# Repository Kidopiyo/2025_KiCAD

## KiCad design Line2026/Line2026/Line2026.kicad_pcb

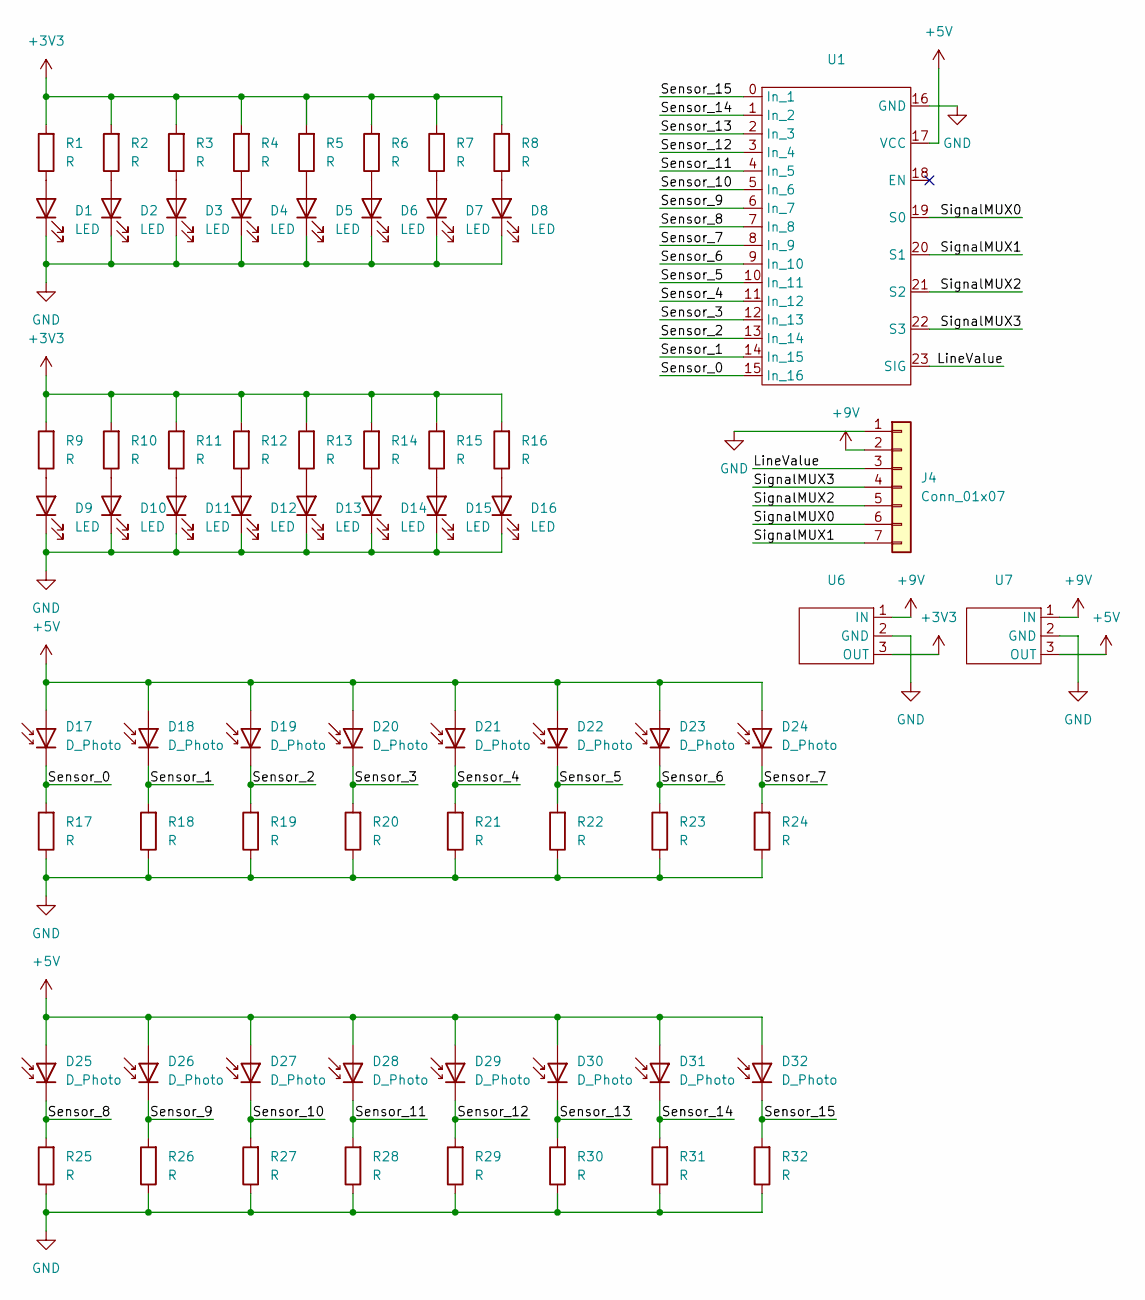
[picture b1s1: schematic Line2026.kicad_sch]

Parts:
D1, D2, D3, D4, D5, D6, D7, D8, D9, D10, D11, D12, D13, D14, D15, D16: LED; LED_D3.0mm
D17, D18, D19, D20, D21, D22, D23, D24, D25, D26, D27, D28, D29, D30, D31, D32: D_Photo; LED_D3.0mm
J4: Conn_01x07; JST_XA_B07B-XASK-1-A_1x07_P2.50mm_Vertical
R1, R2, R3, R4, R5, R6, R7, R8, R9, R10, R11, R12, R13, R14, R15, R16, R17, R18, R19, R20, R21, R22, R23, R24, R25, R26, R27, R28, R29, R30, R31, R32: R; R_Axial_DIN0207_L6.3mm_D2.5mm_P7.62mm_Horizontal
U1: BOB-09056
U6, U7: Akiduki_Converter

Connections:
+3V3: R1.2, R2.2, R3.2, R4.2, R5.2, R6.2, R7.2, R8.2, R9.2, R10.2, R11.2, R12.2, R13.2, R14.2, R15.2, R16.2, U6.3 (OUT)
+5V: D17.2 (A), D18.2 (A), D19.2 (A), D20.2 (A), D21.2 (A), D22.2 (A), D23.2 (A), D24.2 (A), D25.2 (A), D26.2 (A), D27.2 (A), D28.2 (A), D29.2 (A), D30.2 (A), D31.2 (A), D32.2 (A), U1.17 (VCC), U7.3 (OUT)
+9V: J4.2, U6.1 (IN), U7.1 (IN)
/LineValue: J4.3, U1.23 (SIG)
/Sensor_0: D17.1 (K), R17.2, U1.15 (In_16)
/Sensor_1: D18.1 (K), R18.2, U1.14 (In_15)
/Sensor_2: D19.1 (K), R19.2, U1.13 (In_14)
/Sensor_3: D20.1 (K), R20.2, U1.12 (In_13)
/Sensor_4: D21.1 (K), R21.2, U1.11 (In_12)
/Sensor_5: D22.1 (K), R22.2, U1.10 (In_11)
/Sensor_6: D23.1 (K), R23.2, U1.9 (In_10)
/Sensor_7: D24.1 (K), R24.2, U1.8 (In_9)
/Sensor_8: D25.1 (K), R25.2, U1.7 (In_8)
/Sensor_9: D26.1 (K), R26.2, U1.6 (In_7)
/Sensor_10: D27.1 (K), R27.2, U1.5 (In_6)
/Sensor_11: D28.1 (K), R28.2, U1.4 (In_5)
/Sensor_12: D29.1 (K), R29.2, U1.3 (In_4)
/Sensor_13: D30.1 (K), R30.2, U1.2 (In_3)
/Sensor_14: D31.1 (K), R31.2, U1.1 (In_2)
/Sensor_15: D32.1 (K), R32.2, U1.0 (In_1)
/SignalMUX0: J4.6, U1.19 (S0)
/SignalMUX1: J4.7, U1.20 (S1)
/SignalMUX2: J4.5, U1.21 (S2)
/SignalMUX3: J4.4, U1.22 (S3)
GND: D1.1 (K), D2.1 (K), D3.1 (K), D4.1 (K), D5.1 (K), D6.1 (K), D7.1 (K), D8.1 (K), D9.1 (K), D10.1 (K), D11.1 (K), D12.1 (K), D13.1 (K), D14.1 (K), D15.1 (K), D16.1 (K), J4.1, R17.1, R18.1, R19.1, R20.1, R21.1, R22.1, R23.1, R24.1, R25.1, R26.1, R27.1, R28.1, R29.1, R30.1, R31.1, R32.1, U1.16 (GND), U6.2 (GND), U7.2 (GND)
unnamed: D1.2 (A), R1.1
unnamed: D2.2 (A), R2.1
unnamed: D3.2 (A), R3.1
unnamed: D4.2 (A), R4.1
unnamed: D5.2 (A), R5.1
unnamed: D6.2 (A), R6.1
unnamed: D7.2 (A), R7.1
unnamed: D8.2 (A), R8.1
unnamed: D9.2 (A), R9.1
unnamed: D10.2 (A), R10.1
unnamed: D11.2 (A), R11.1
unnamed: D12.2 (A), R12.1
unnamed: D13.2 (A), R13.1
unnamed: D14.2 (A), R14.1
unnamed: D15.2 (A), R15.1
unnamed: D16.2 (A), R16.1

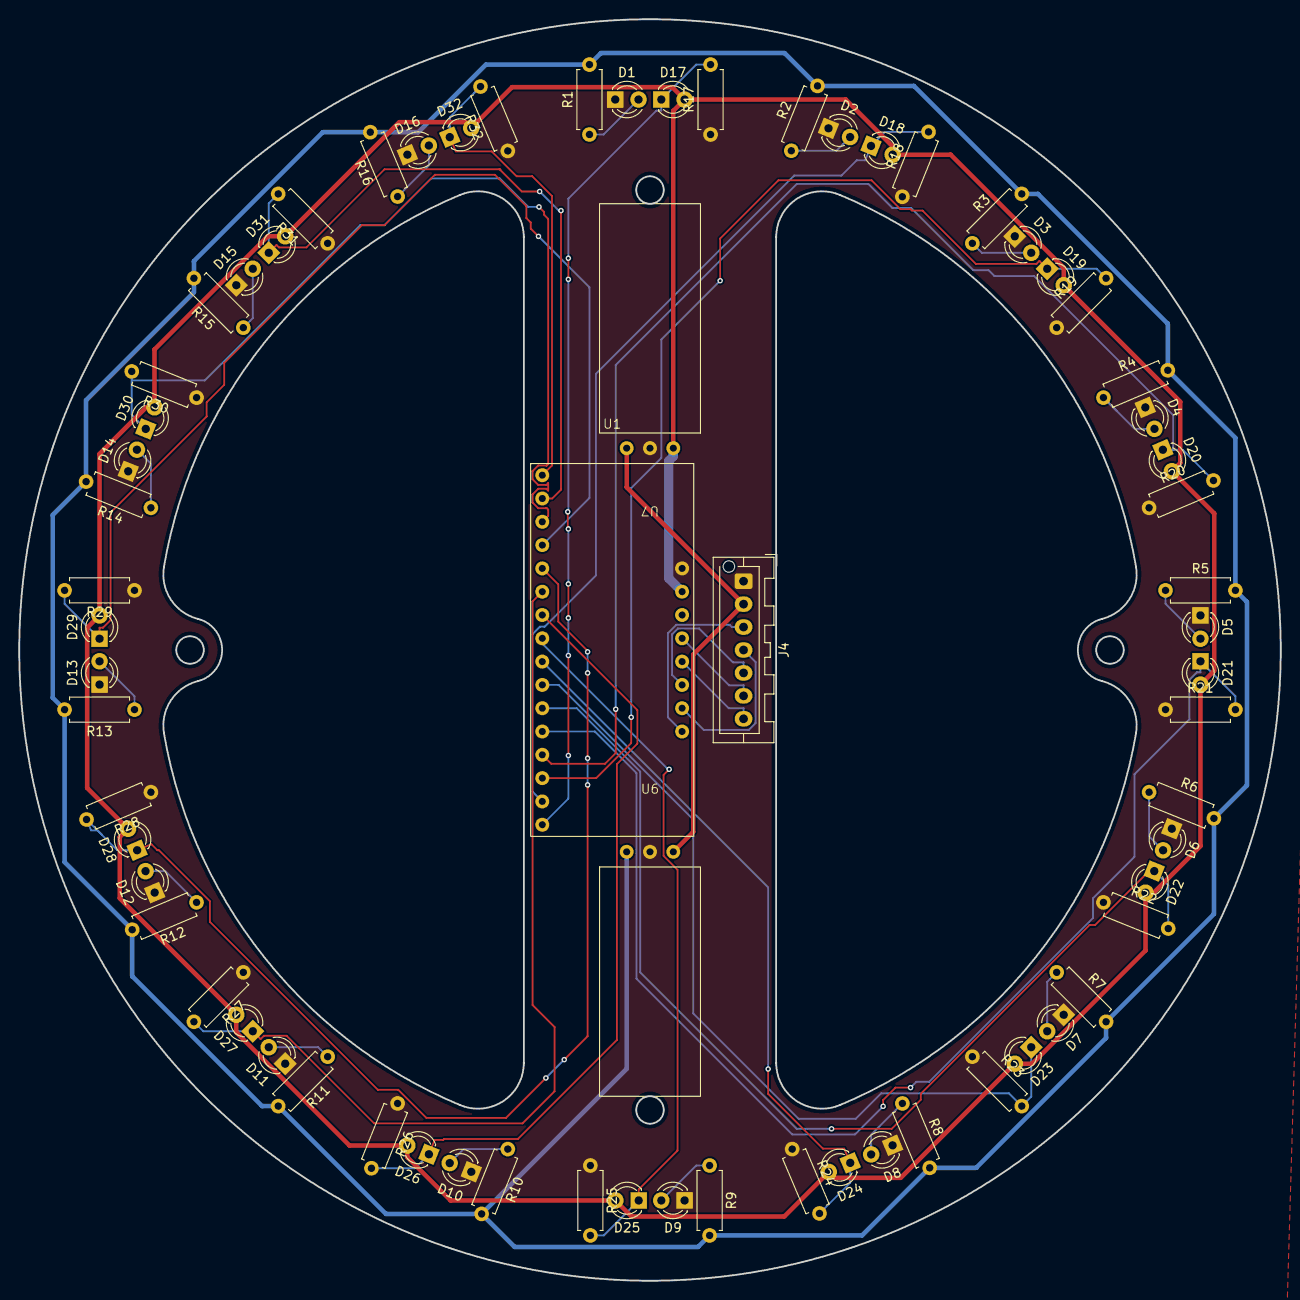
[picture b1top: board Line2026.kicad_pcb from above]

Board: 2 copper layers, 137.5 x 137.5 mm, 68 parts (0 on the bottom side), 41 nets.

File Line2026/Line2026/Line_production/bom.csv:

Designator,Footprint,Quantity,Value,LCSC Part #
"D1, D10, D11, D12, D13, D14, D15, D16, D2, D3, D4, D5, D6, D7, D8, D9",LED_D3.0mm,16,LED,
"D17, D18, D19, D20, D21, D22, D23, D24, D25, D26, D27, D28, D29, D30, D31, D32",LED_D3.0mm,16,D_Photo,
J4,JST_XA_B07B-XASK-1-A_1x07_P2.50mm_Vertical,1,Conn_01x07,
"R1, R10, R11, R12, R13, R14, R15, R16, R17, R18, R19, R2, R20, R21, R22, R23, R24, R25, R26, R27, R28, R29, R3, R30, R31, R32, R4, R5, R6, R7, R8, R9",R_Axial_DIN0207_L6.3mm_D2.5mm_P7.62mm_Horizontal,32,R,
U1,BOB-09056,1,~,
"U6, U7",Akiduki_Converter,2,~,

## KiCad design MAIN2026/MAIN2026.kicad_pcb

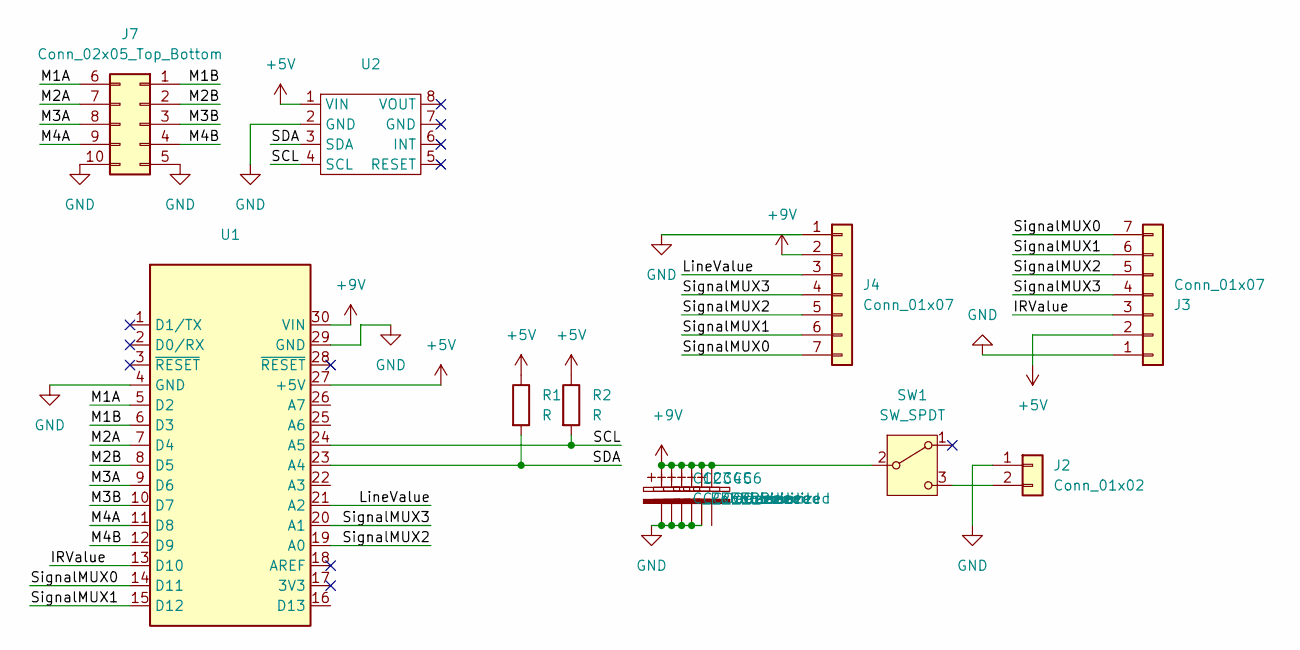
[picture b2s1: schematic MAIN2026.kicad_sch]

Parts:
C1, C2, C3, C4, C5, C6: C_Polarized; CP_Radial_D8.0mm_P2.50mm
J2: Conn_01x02; JST_XA_B02B-XASK-1-A_1x02_P2.50mm_Vertical
J3, J4: Conn_01x07; JST_XA_B07B-XASK-1-A_1x07_P2.50mm_Vertical
J7: Conn_02x05_Top_Bottom; XAD_5x2
R1, R2: R; R_Axial_DIN0207_L6.3mm_D2.5mm_P7.62mm_Horizontal
SW1: SW_SPDT; PinHeader_1x03_P2.54mm_Vertical
U1: Arduino_Nano
U2: BNO055

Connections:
+5V: J3.2, R1.1, R2.1, U1.27 (+5V), U2.1 (VIN)
+9V: C1.1, C2.1, C3.1, C4.1, C5.1, C6.1, J4.2, SW1.2 (B), U1.30 (VIN)
/IRValue: J3.3, U1.13 (D10)
/LineValue: J4.3, U1.21 (A2)
/M1A: J7.6, U1.5 (D2)
/M1B: J7.1, U1.6 (D3)
/M2A: J7.7, U1.7 (D4)
/M2B: J7.2, U1.8 (D5)
/M3A: J7.8, U1.9 (D6)
/M3B: J7.3, U1.10 (D7)
/M4A: J7.9, U1.11 (D8)
/M4B: J7.4, U1.12 (D9)
/SCL: R2.2, U1.24 (A5), U2.4 (SCL)
/SDA: R1.2, U1.23 (A4), U2.3 (SDA)
/SignalMUX0: J3.7, J4.7, U1.14 (D11)
/SignalMUX1: J3.6, J4.6, U1.15 (D12)
/SignalMUX2: J3.5, J4.5, U1.19 (A0)
/SignalMUX3: J3.4, J4.4, U1.20 (A1)
GND: C1.2, C2.2, C3.2, C4.2, C5.2, J2.1, J3.1, J4.1, J7.5, J7.10, U1.4 (GND), U1.29 (GND), U2.2 (GND)
unnamed: J2.2, SW1.3 (C)

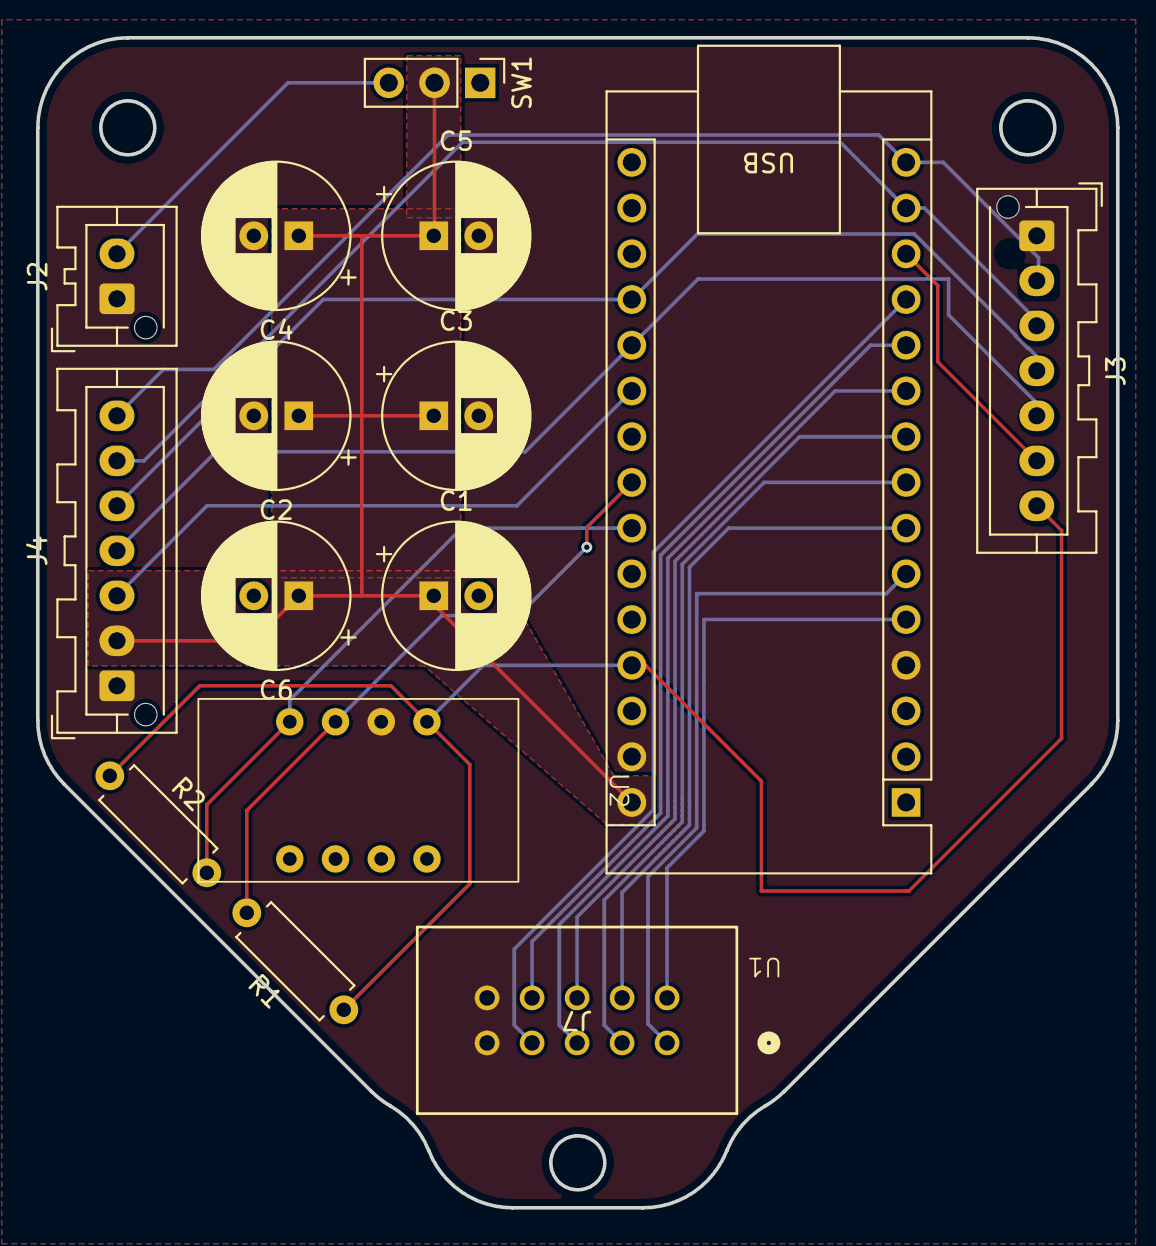
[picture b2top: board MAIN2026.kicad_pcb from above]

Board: 2 copper layers, 60.0 x 65.0 mm, 15 parts (0 on the bottom side), 20 nets.

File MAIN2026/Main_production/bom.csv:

Designator,Footprint,Quantity,Value,LCSC Part #
"C1, C2, C3, C4, C5, C6",CP_Radial_D8.0mm_P2.50mm,6,C_Polarized,
J2,JST_XA_B02B-XASK-1-A_1x02_P2.50mm_Vertical,1,Conn_01x02,
"J3, J4",JST_XA_B07B-XASK-1-A_1x07_P2.50mm_Vertical,2,Conn_01x07,
J7,XAD_5x2,1,Conn_02x05_Top_Bottom,
"R1, R2",R_Axial_DIN0207_L6.3mm_D2.5mm_P7.62mm_Horizontal,2,R,
SW1,PinHeader_1x03_P2.54mm_Vertical,1,SW_SPDT,
U1,Arduino_Nano,1,~,
U2,BNO055,1,~,

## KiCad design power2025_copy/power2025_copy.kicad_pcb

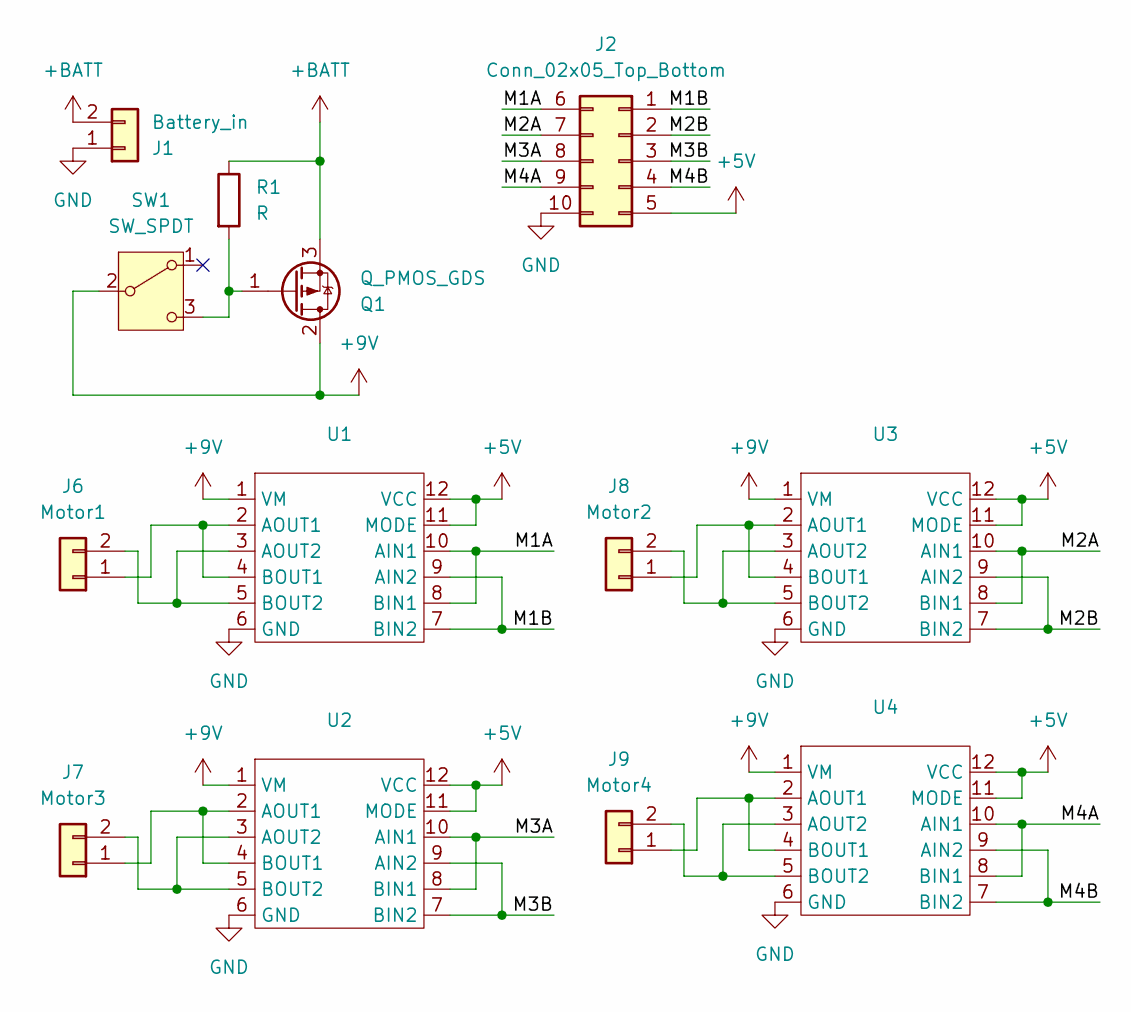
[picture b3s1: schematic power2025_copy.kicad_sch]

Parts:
J1: Battery_in; JST_XH_B2B-XH-A_1x02_P2.50mm_Vertical
J2: Conn_02x05_Top_Bottom; XAD_5x2
J6: Motor1; JST_XH_B2B-XH-A_1x02_P2.50mm_Vertical
J7: Motor3; JST_XH_B2B-XH-A_1x02_P2.50mm_Vertical
J8: Motor2; JST_XH_B2B-XH-A_1x02_P2.50mm_Vertical
J9: Motor4; JST_XH_B2B-XH-A_1x02_P2.50mm_Vertical
Q1: Q_PMOS_GDS; TO-3P-3_Horizontal_TabDown
R1: R; R_Axial_DIN0207_L6.3mm_D2.5mm_P7.62mm_Horizontal
SW1: SW_SPDT; PinHeader_1x03_P2.54mm_Vertical
U1, U2, U3, U4: DRV8835

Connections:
+5V: J2.5, U1.11 (MODE), U1.12 (VCC), U2.11 (MODE), U2.12 (VCC), U3.11 (MODE), U3.12 (VCC), U4.11 (MODE), U4.12 (VCC)
+9V: Q1.2 (D), SW1.2 (B), U1.1 (VM), U2.1 (VM), U3.1 (VM), U4.1 (VM)
+BATT: J1.2, Q1.3 (S), R1.1
/M1A: J2.6, U1.8 (BIN1), U1.10 (AIN1)
/M1B: J2.1, U1.7 (BIN2), U1.9 (AIN2)
/M2A: J2.7, U3.8 (BIN1), U3.10 (AIN1)
/M2B: J2.2, U3.7 (BIN2), U3.9 (AIN2)
/M3A: J2.8, U2.8 (BIN1), U2.10 (AIN1)
/M3B: J2.3, U2.7 (BIN2), U2.9 (AIN2)
/M4A: J2.9, U4.8 (BIN1), U4.10 (AIN1)
/M4B: J2.4, U4.7 (BIN2), U4.9 (AIN2)
GND: J1.1, J2.10, U1.6 (GND), U2.6 (GND), U3.6 (GND), U4.6 (GND)
unnamed: J6.1, U1.2 (AOUT1), U1.4 (BOUT1)
unnamed: J6.2, U1.3 (AOUT2), U1.5 (BOUT2)
unnamed: J7.1, U2.2 (AOUT1), U2.4 (BOUT1)
unnamed: J7.2, U2.3 (AOUT2), U2.5 (BOUT2)
unnamed: J8.1, U3.2 (AOUT1), U3.4 (BOUT1)
unnamed: J8.2, U3.3 (AOUT2), U3.5 (BOUT2)
unnamed: J9.1, U4.2 (AOUT1), U4.4 (BOUT1)
unnamed: J9.2, U4.3 (AOUT2), U4.5 (BOUT2)
unnamed: Q1.1 (G), R1.2, SW1.3 (C)

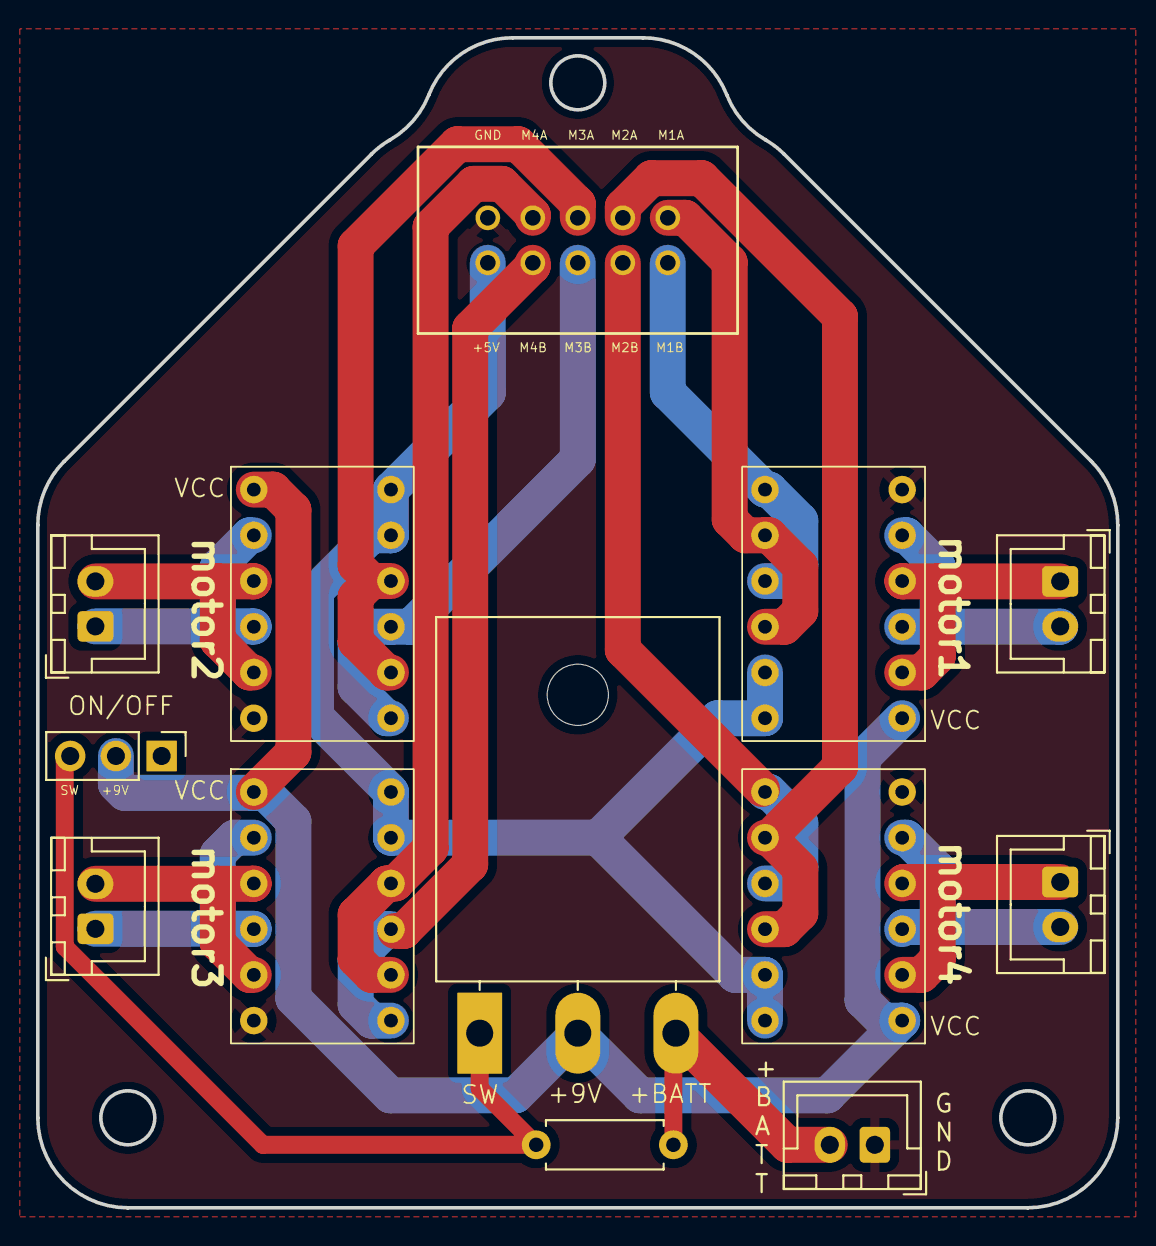
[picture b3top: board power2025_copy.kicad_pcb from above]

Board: 2 copper layers, 60.0 x 65.0 mm, 13 parts (0 on the bottom side), 21 nets.

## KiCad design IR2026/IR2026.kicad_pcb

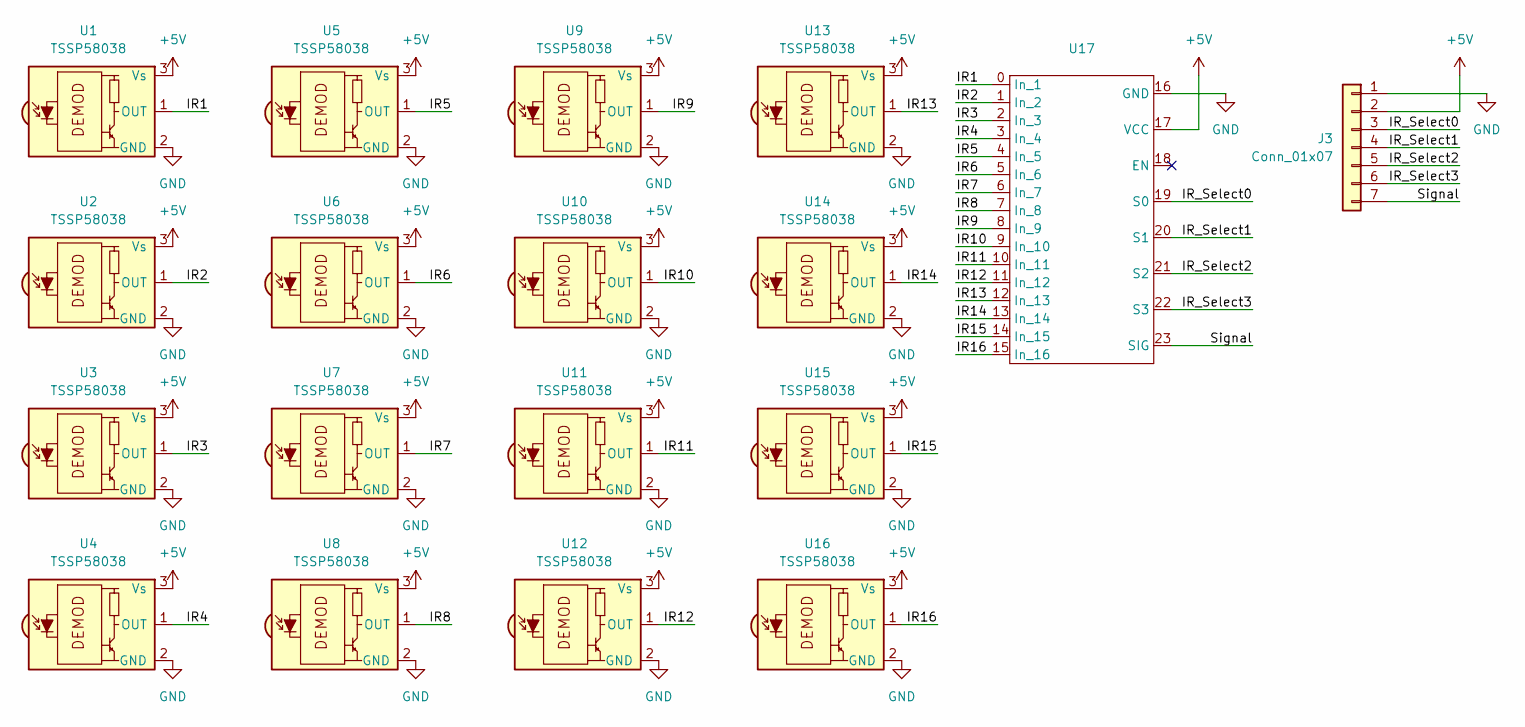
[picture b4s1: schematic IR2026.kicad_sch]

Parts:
J3: Conn_01x07; JST_XA_B07B-XASK-1-A_1x07_P2.50mm_Vertical
U1, U2, U3, U4, U5, U6, U7, U8, U9, U10, U11, U12, U13, U14, U15, U16: TSSP58038; Vishay_MINIMOLD-3Pin
U17: BOB-09056

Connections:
+5V: J3.2, U1.3 (Vs), U2.3 (Vs), U3.3 (Vs), U4.3 (Vs), U5.3 (Vs), U6.3 (Vs), U7.3 (Vs), U8.3 (Vs), U9.3 (Vs), U10.3 (Vs), U11.3 (Vs), U12.3 (Vs), U13.3 (Vs), U14.3 (Vs), U15.3 (Vs), U16.3 (Vs), U17.17 (VCC)
/IR1: U1.1 (OUT), U17.0 (In_1)
/IR2: U2.1 (OUT), U17.1 (In_2)
/IR3: U3.1 (OUT), U17.2 (In_3)
/IR4: U4.1 (OUT), U17.3 (In_4)
/IR5: U5.1 (OUT), U17.4 (In_5)
/IR6: U6.1 (OUT), U17.5 (In_6)
/IR7: U7.1 (OUT), U17.6 (In_7)
/IR8: U8.1 (OUT), U17.7 (In_8)
/IR9: U9.1 (OUT), U17.8 (In_9)
/IR10: U10.1 (OUT), U17.9 (In_10)
/IR11: U11.1 (OUT), U17.10 (In_11)
/IR12: U12.1 (OUT), U17.11 (In_12)
/IR13: U13.1 (OUT), U17.12 (In_13)
/IR14: U14.1 (OUT), U17.13 (In_14)
/IR15: U15.1 (OUT), U17.14 (In_15)
/IR16: U16.1 (OUT), U17.15 (In_16)
/IR_Select0: J3.3, U17.19 (S0)
/IR_Select1: J3.4, U17.20 (S1)
/IR_Select2: J3.5, U17.21 (S2)
/IR_Select3: J3.6, U17.22 (S3)
/Signal: J3.7, U17.23 (SIG)
GND: J3.1, U1.2 (GND), U2.2 (GND), U3.2 (GND), U4.2 (GND), U5.2 (GND), U6.2 (GND), U7.2 (GND), U8.2 (GND), U9.2 (GND), U10.2 (GND), U11.2 (GND), U12.2 (GND), U13.2 (GND), U14.2 (GND), U15.2 (GND), U16.2 (GND), U17.16 (GND)

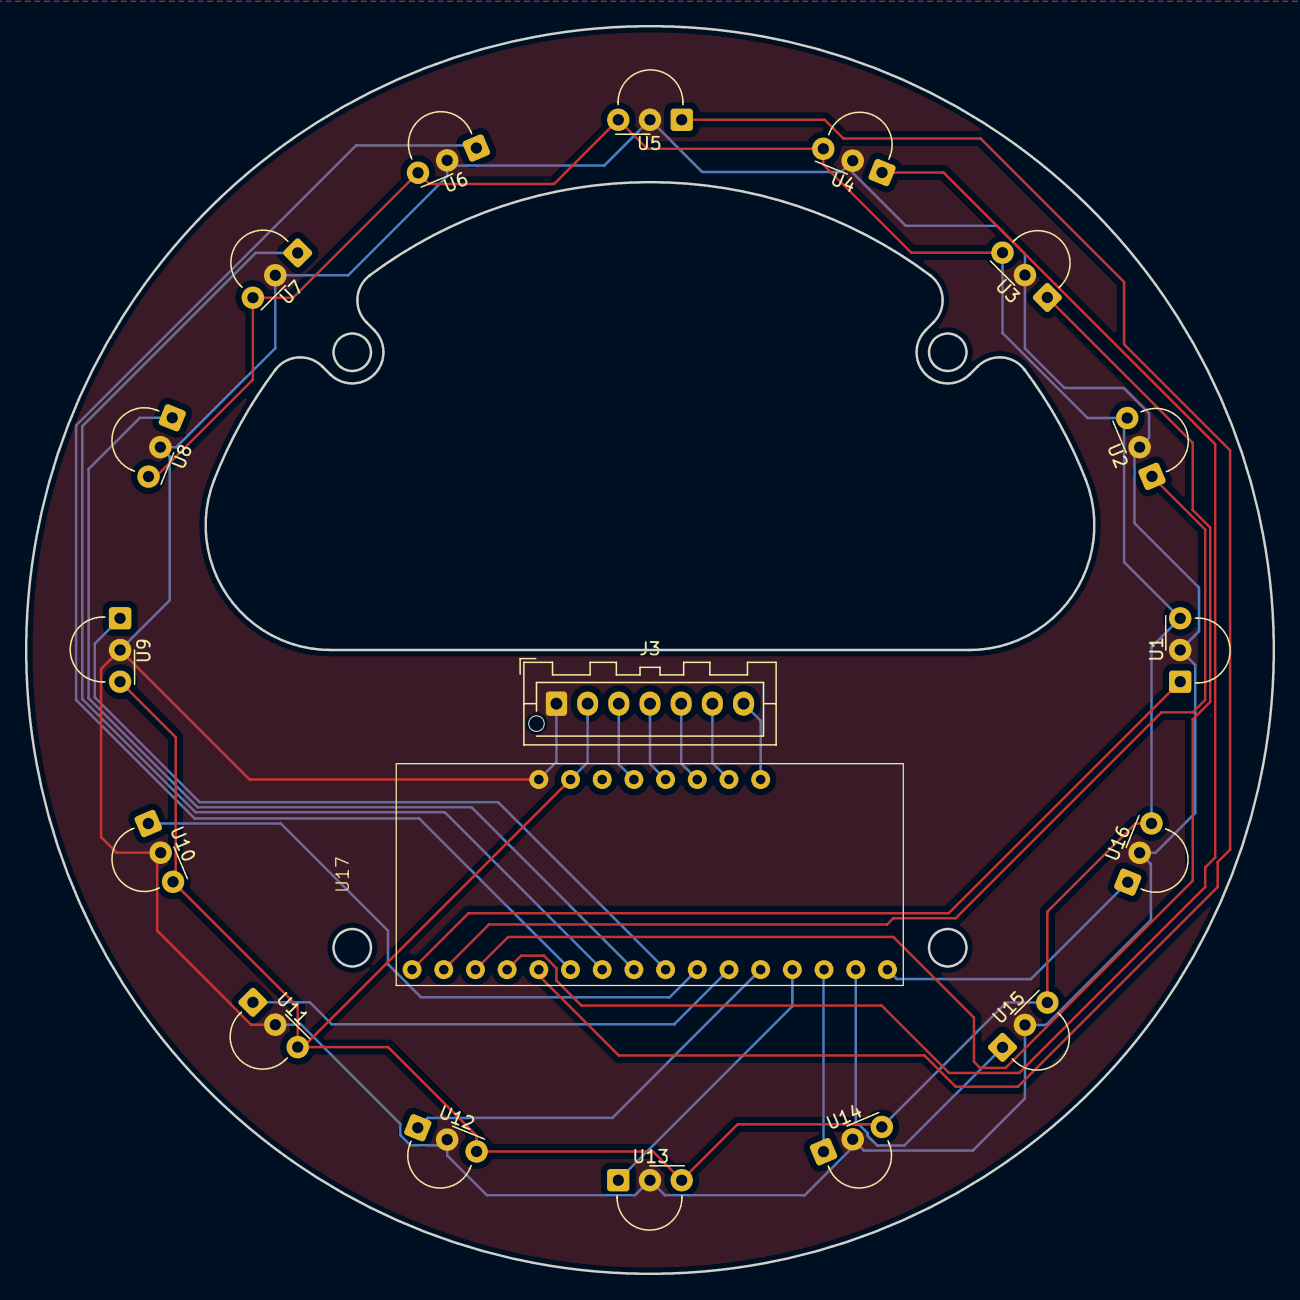
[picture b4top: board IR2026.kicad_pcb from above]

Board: 2 copper layers, 100.0 x 100.0 mm, 18 parts (0 on the bottom side), 23 nets.

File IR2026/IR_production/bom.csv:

Designator,Footprint,Quantity,Value,LCSC Part #
J3,JST_XA_B07B-XASK-1-A_1x07_P2.50mm_Vertical,1,Conn_01x07,
"U1, U10, U11, U12, U13, U14, U15, U16, U2, U3, U4, U5, U6, U7, U8, U9",Vishay_MINICAST-3Pin,16,TSSP58038,
U17,BOB-09056,1,~,

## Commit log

2025-12-06 init
2025-12-06 パワー基板にコンデンサーを追加
